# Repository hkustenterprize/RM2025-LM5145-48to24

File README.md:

# RM2025-LM5145-48to24
https://bbs.robomaster.com/article/760956?source=8

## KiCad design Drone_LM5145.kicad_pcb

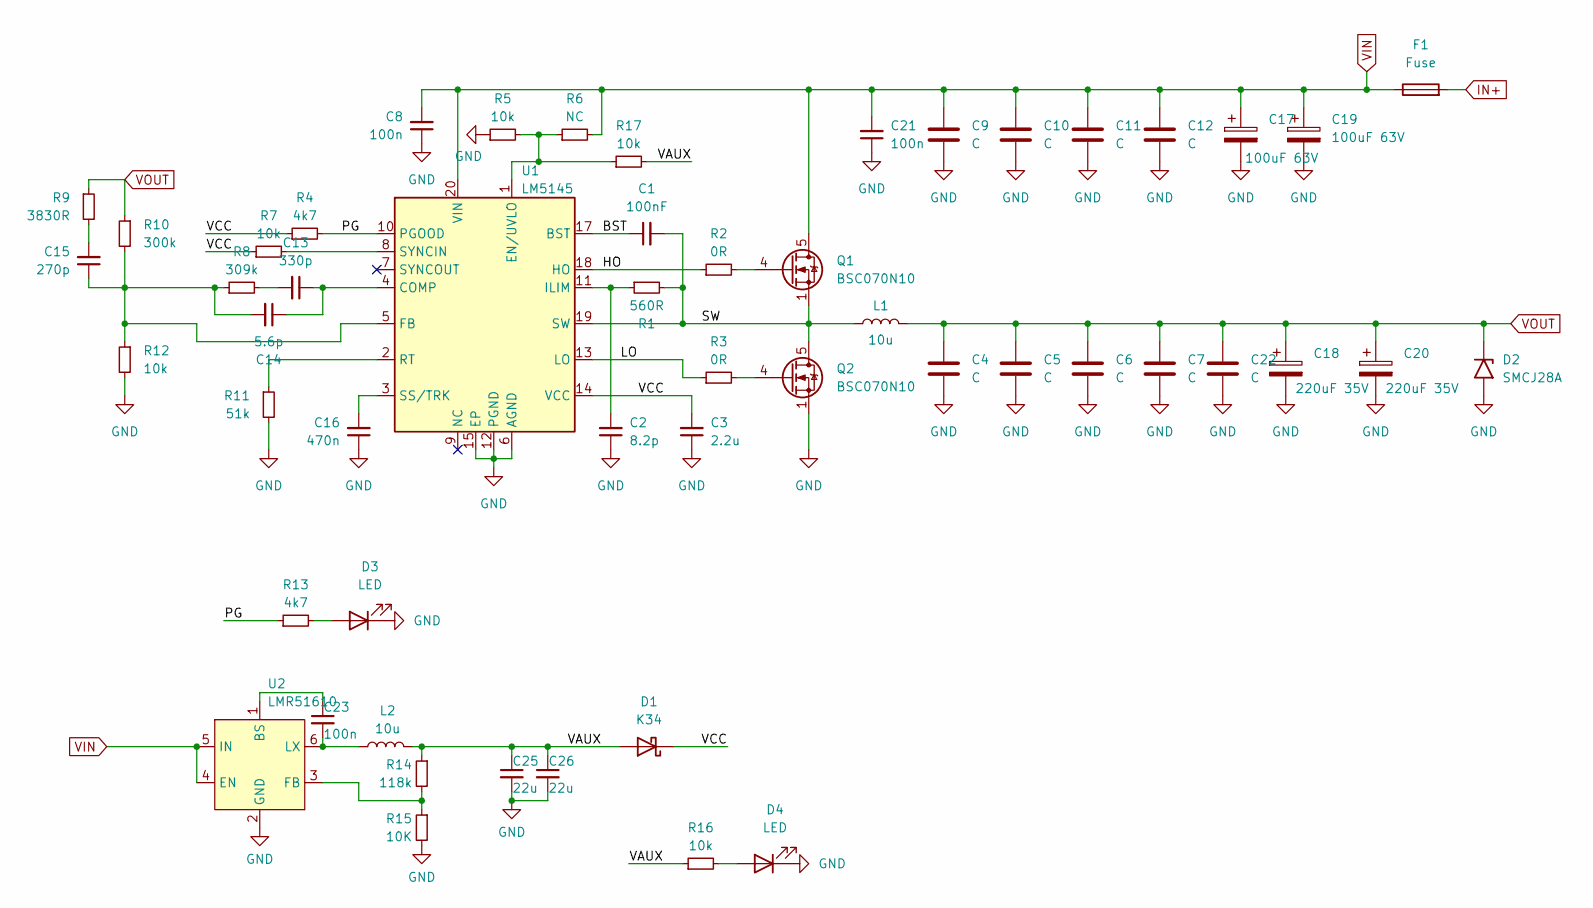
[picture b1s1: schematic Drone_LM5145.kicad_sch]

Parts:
C1: 100nF; C_0603_1608Metric
C2: 8.2p; C_0603_1608Metric
C3: 2.2u; C_0603_1608Metric
C4, C5, C6, C7, C22: C; C_1206_3216Metric
C8, C21, C23: 100n; C_0603_1608Metric
C9, C10, C11, C12: C; C_1210_3225Metric
C13: 330p; C_0603_1608Metric
C14: 5.6p; C_0603_1608Metric
C15: 270p; C_0603_1608Metric
C16: 470n; C_0603_1608Metric
C17, C19: 100uF 63V; CP_Radial_D8.0mm_P3.50mm
C18, C20: 220uF 35V; CP_Radial_D8.0mm_P3.50mm
C25, C26: 22u; C_0805_2012Metric
D1: K34; D_SMF
D2: SMCJ28A; D_SMC
D3, D4: LED; LED_0603_1608Metric
F1: Fuse; Fuse_Littelfuse-NANO2-451_453
L1: 10u; PQ2014_10uH
L2: 10u; L_Sunlord_MWSA0402S
Q1, Q2: BSC070N10; TDSON-8-1
R1: 560R; R_0603_1608Metric
R2, R3: 0R; R_0603_1608Metric
R4, R13: 4k7; R_0603_1608Metric
R5, R7, R12, R16, R17: 10k; R_0603_1608Metric
R6: NC; R_0603_1608Metric
R8: 309k; R_0603_1608Metric
R9: 3830R; R_0603_1608Metric
R10: 300k; R_0603_1608Metric
R11: 51k; R_0603_1608Metric
R14: 118k; R_0603_1608Metric
R15: 10K; R_0603_1608Metric
U1: LM5145; Texas_RGY_R-PVQFN-N20_EP2.05x3.05mm
U2: LMR51610; SOT-23-6

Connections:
/BST: C1.1, U1.17 (BST)
/HO: R2.1, U1.18 (HO)
/LO: R3.1, U1.13 (LO)
/PG: R4.2, R13.1, U1.10 (PGOOD)
/SW: C1.2, L1.1, Q1.1 (S), Q1.2 (S), Q1.3 (S), Q2.5 (D), R1.2, U1.19 (SW)
/VAUX: C25.1, C26.1, D1.2 (A), L2.2, R14.1, R16.1, R17.2
/VCC: C3.2, D1.1 (K), R4.1, R7.1, U1.14 (VCC)
GND: C2.1, C3.1, C4.2, C5.2, C6.2, C7.2, C8.1, C9.2, C10.2, C11.2, C12.2, C16.1, C17.2, C18.2, C19.2, C20.2, C21.1, C22.2, C25.2, C26.2, D2.2 (A2), D3.1 (K), D4.1 (K), Q2.1 (S), Q2.2 (S), Q2.3 (S), R5.1, R11.2, R12.2, R15.2, U1.6 (AGND), U1.12 (PGND), U1.15 (EP), U1.21 (EP), U2.2 (GND)
IN+: F1.2
unnamed: C13.2, R8.2
unnamed: C15.2, R9.2
unnamed: D3.2 (A), R13.2
unnamed: D4.2 (A), R16.2
unnamed: Q1.4 (G), R2.2
unnamed: Q2.4 (G), R3.2
unnamed: C13.1, C14.1, U1.4 (COMP)
unnamed: R5.2, R6.1, R17.1, U1.1 (EN/UVLO)
unnamed: C14.2, C15.1, R8.1, R10.2, R12.1, U1.5 (FB)
unnamed: C2.2, R1.1, U1.11 (ILIM)
unnamed: R11.1, U1.2 (RT)
unnamed: C16.2, U1.3 (SS/TRK)
unnamed: R7.2, U1.8 (SYNCIN)
unnamed: C23.1, U2.1 (BS)
unnamed: R14.2, R15.1, U2.3 (FB)
unnamed: C23.2, L2.1, U2.6 (LX)
VIN: C8.2, C9.1, C10.1, C11.1, C12.1, C17.1, C19.1, C21.2, F1.1, Q1.5 (D), R6.2, U1.20 (VIN), U2.4 (EN), U2.5 (IN)
VOUT: C4.1, C5.1, C6.1, C7.1, C18.1, C20.1, C22.1, D2.1 (A1), L1.2, R9.1, R10.1

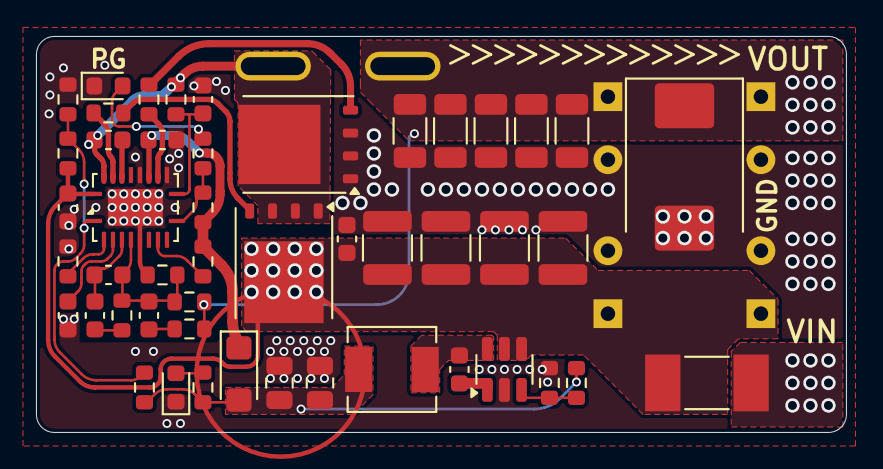
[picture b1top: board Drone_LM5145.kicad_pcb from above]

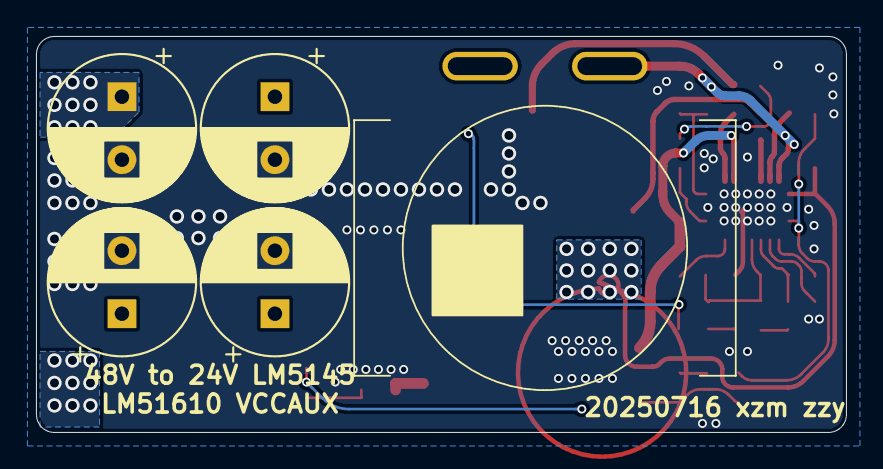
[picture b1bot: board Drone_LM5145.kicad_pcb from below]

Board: 2 copper layers, 45.0 x 22.0 mm, 53 parts (5 on the bottom side), 26 nets.

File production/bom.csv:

Designator,Footprint,Quantity,Value,LCSC Part #
C1,0603,1,100nF,
"C10, C11, C12, C9",1210,4,C,
C13,0603,1,330p,
C14,0603,1,5.6p,
C15,0603,1,270p,
C16,0603,1,470n,
"C17, C19",CP_Radial_D8.0mm_P3.50mm,2,100uF 63V,
"C18, C20",CP_Radial_D8.0mm_P3.50mm,2,220uF 35V,
C2,0603,1,8.2p,
"C21, C23, C8",0603,3,100n,
"C22, C4, C5, C6, C7",1206,5,C,
"C25, C26",0805,2,22u,
C3,0603,1,2.2u,
D1,D_SMF,1,K34,
D2,D_SMC,1,SMCJ28A,
"D3, D4",0603,2,LED,
F1,Fuse_Littelfuse-NANO2-451_453,1,Fuse,
L1,PQ2014_10uH,1,10u,
L2,L_Sunlord_MWSA0402S,1,10u,
"Q1, Q2",TDSON-8-1,2,BSC070N10,
R1,0603,1,560R,
R10,0603,1,300k,
R11,0603,1,51k,
"R12, R15, R16, R17, R5, R7",0603,6,10k,
"R13, R4",0603,2,4k7,
R14,0603,1,118k,
"R2, R3",0603,2,0R,
R6,0603,1,NC,
R8,0603,1,309k,
R9,0603,1,3830R,
U1,Texas_RGY_R-PVQFN-N20_EP2.05x3.05mm,1,LM5145,
U2,SOT-23-6,1,LMR51610,

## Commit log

2025-07-31 工程文件
2025-07-31 更新ibom和加工文件
